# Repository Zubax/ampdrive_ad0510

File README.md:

# AmpDrive AD0510 / Zubax Komar

Zubax Komar is a high-quality FOC ESC based on [Telega](https://zubax.com/technologies/telega) motor control technology.
Komar is designed to support the propulsion systems of light unmanned aerial vehicles (UAVs), unmanned underwater vehicles (UUVs)
and unmanned surface vehicles (USVs). Komar is compatible with almost all PMSM and BLDC motors.
It is designed to be a part of an integrated drive but allows operation as a separate unit as well.
Komar is one of the reference designs for the [Mitochondrik LV](https://zubax.com/products/mitochondrik-lv) control module.

## Brief specs

* 12...51 V input voltage range (4...12S LiCoO<sub>2</sub> battery).
* Up to 2500 W output power (with 12S LiCoO<sub>2</sub> battery).
* Maximum continuous phase current amplitude 100 A.
* A software-controllable 5 V BEC.
* Built-in motor temperature sensor for enhanced self-diagnostics.
* Komar supports a rich set of communication interfaces:
  * Double redundant CAN bus interface.
  * USB Micro-B interface for control, management, and telemetry.
  * Industry-standard RC PWM input.
* Komar is built using highly reliable automotive-grade AEC-Q qualified components.
* Operating device temperature - -40..85 °C.
* Operating humidity - 0..100 %RH (Condensation not permitted).
* Weight - 96.5 g (cables not included).

Due to its superb efficiency, Komar can operate at high power levels using only a very lightweight and compact heatsink to cool the device down.

Komar is designed to be a part of an integrated drive for mid-power motors.
It is best suited for motors with the following specs:

* Continuous power: 2.5 kW
* Continuous phase current amplitude: 90 A
* Outer diameter: 80 mm

Komar can also be used as a separate unit. In this case, a custom phase connector mounted on the housing may be used to provide motor connections.

The parameters of the Aux port are as follows:

* $V_\text{pull}=3.3V$ (defined by Mitochondrik)
* $R_\text{pull}=1200\Omega$ (defined by Mitochondrik)
* $R_\text{io}=200\Omega$ at the Aux connector
* $R_\text{io}=0\Omega$ at the through-hole motor thermistor pin on the PCB (see schematics)

## Construction and usage

Komar itself consists of a power stage PCB with Mitochondrik and the housing (aluminum enclosure plus several plastic parts).
The PCB may use several optional 3D-printed parts that don't influence its properties directly, but may improve the overall user experience:

- Lightpipe
- Capacitor support

## Connections and indication

All connections (except the phase connector) and indicators are presented on the bottom cover, as shown in figure below.

Pinout of connectors is presented in the tables below. 

### CAN1 & CAN2 connectors (type JST BM04B-GHS)

| Pin # | Type  | Name  | Comments                                        |
|-------|-------|-------|-------------------------------------------------|
| 1     | Power | PWR   | BEC 5V power output. Activated in the firmware. |
| 2     | I/O   | CAN_H |                                                 |
| 3     | I/O   | CAN_L |                                                 |
| 4     | Power | GND   |                                                 |

The device does not terminate the CAN bus internally.
If the bus is not redundant, only CAN1 (the primary CAN bus interface) can be used.

### AUX connector (type JST BM04B-GHS)

| Pin # | Type  | Name  | Comments                          |
|-------|-------|-------|-----------------------------------|
| 1     | Power | PWR   | 5V line output                    |
| 2     | I/O   | GPIO1 | GPIO/RCPWM input/Thermistor input |
| 3     | I/O   | GPIO2 |                                   |
| 4     | Power | GND   |                                   |

The motor windings temperature can be measured by means of a PTC thermistor. The following thermistors can be connected between GPIO1 and GND:

- KTY84/130
- KTY81/120
- KTY83/120

No additional components are needed for the thermistor. The thermistor model is selected in the firmware.

### USB connector

Common USB 2.0 Micro-USB connector is dedicated for the device configuration and control using the [Kucher GUI](https://files.zubax.com/products/com.zubax.kucher/1.0.0/).

## Thermal performance

Thermal simulation is performed under the following conditions:

* The heat source is applied to the heatsink area where the PCB is placed. Its power is 78.5 W.
  It is a typical value of power losses in the Komar power stage when operating at a power level of 2500 W
  and powered from a discharged 12S battery (~40 V). This should represent the worst-case scenario.

* Ambient temperature is 20 °C.

* The convection value of 350 W/(m<sup>2</sup>K) is established empirically after conducting several experiments with real hardware.

## Mounting pattern

## VSI Configuration

All Komars with Telega v1 (Cyphal) are configured with the following VSI parameters by default.

```
sys.golden:               sys. vsi.
vsi.bridge_resistance:    [0.002, 0.003, 0.002, 0.003, 0.002, 0.002]
vsi.phase_current_gain:   [100, 100,  25,  25]
vsi.phase_current_stderr: [0.3, 0.3, 0.2, 0.2]
vsi.thermistor_v2k:       [223.15, 100.0, 0.0]
```

Please refer to the manufacturing manual and schematics for further information.
The most up-to-date documentation is attached to the latest published
[release package](https://github.com/Zubax/Komar/releases).

## Release notes

Newest entries at the top.

### Komar v1.6 (work in progress)

* The USB connector will no longer be installed, as USB is not supported in Telega v1.
* to be continued...

### Komar v1.5 (January 2023)

* Updated alternative for MCP9700AT-E/TTVAO to MCP9700T-E/TT.

### Komar v1.4 (January 2023)

* Removed alternative for Diode BAV99HDWQ-13.
* Increased the hardware over-current protection trip level to 427A.

### Komar v1.3 (November 2022)

* Changed DC/Battery power wire to 12 AWG in the assembly manual.
* Corrected Micro USB attributes in the schematic.
* Added alternative parts:

| Part               | Alternative       | Function          |
| -------------------| ------------------| ------------------|
| ATA6561-GBQW-N     | TJA1441DTK/0Z     | CAN TRANSCEIVER   |
| FDMS86368-F085     | BSC080N12LSGATMA1 | FET               |
| BAV99HDWQ-13       | BAV70HDWQ-13      | DIODE             |
| MCP9700AT-E/TTVAO  | MCP9701T-E/TT     | THERMISTOR        |
| ELXZ630ELL331MK20S | EEU-FC1J331B      | CAPACITOR         |
| NRVB120VLSFT1G     | NRVB230LSFT1G     | DIODE             |

### Komar v1.2 (July 2021)

* USB connector with mounting pads swaped with through-hole USB connector to ensure durability.
* Manufacturing instructions update.
* New design of the phase connector.
* Phase connector manufacturing instructions and jig added.
* A better design of the PCB spacer added.

### Komar v1.1 (August 2020)

* Panel template fix: solder mask issue with phase connectors pads fixed (#13).
* Enclosure: increase chamfering depth (#14).

### Komar v1.0 (July 2020)

#### Major PCB updates

* All components are AEC-Q qualified to be compatible with the hardware design policies.
* Better and bigger bulk capacitors.
* Holes for adding 3D-printed capacitor supports added; capacitor supports  developed (not shown on the PCB).
* All the gate networks re-routed and greatly improved.
* All the LEDs grouped in one place; holes for mounting lightpipe added.
* Holes diameter for power supply wires soldering greatly increased to fit any 3.3 sqmm multi-stand wire.
* Holes diameter for phase wires increased to fit either any 2 sqmm multi-stand wire
  (in the case of motor soldering to the PCB) or 3.3 sqmm single-strand wire (if phase connectors are used).
* Overcurrent protection trip level increased 1.5 times to theoretical value of 200 A.
  In practice, however, the overcurrent protection tends to trip at approx. 20-30% below the configured level
  due to the temperature drift of the MOSFETs R<sub>DS(on)</sub> and RF noise.
* TVS diodes with a lower reverse standoff voltage are used (51 V).

#### Major housing changes

* The housing parts are now held together with 4 M3.5 screws instead of M3.
* The housing itself is now mounted on the chassis using 4x M4 screws (was M3).
* Wall thickness of the top part of the housing increased from 1 to 1.6 mm.
* The connector window is slightly smaller now.
* A totally different construction of the phase connector.
  It is much bigger and accepts bullet connectors up to 6 mm (previously, 3.5 mm bullet connectors were used).
* Phase connector is now supposed to use single-stranded thick stiff copper wires instead of flexible multi-stranded ones.
* All the LEDs are grouped in one place now. The holes for the LEDs have been moved.
* Lightpipe for the LEDs added (will be manufactured inhouse using 3d printing).
* 3D-printed spacers between the PCB and the housing added.
* Slightly improved the heatsink efficiency by redesigning the fins.
* 3x M2.5 holes for mounting optional (and not yet developed) connector protection cap added.
* Optional power connector assembly  mount added.

### Komar v0.2 (2018)

First release that was actually manufactured.

### License

This project is licensed under the terms of [CC-BY 4.0](https://creativecommons.org/licenses/by/4.0/).

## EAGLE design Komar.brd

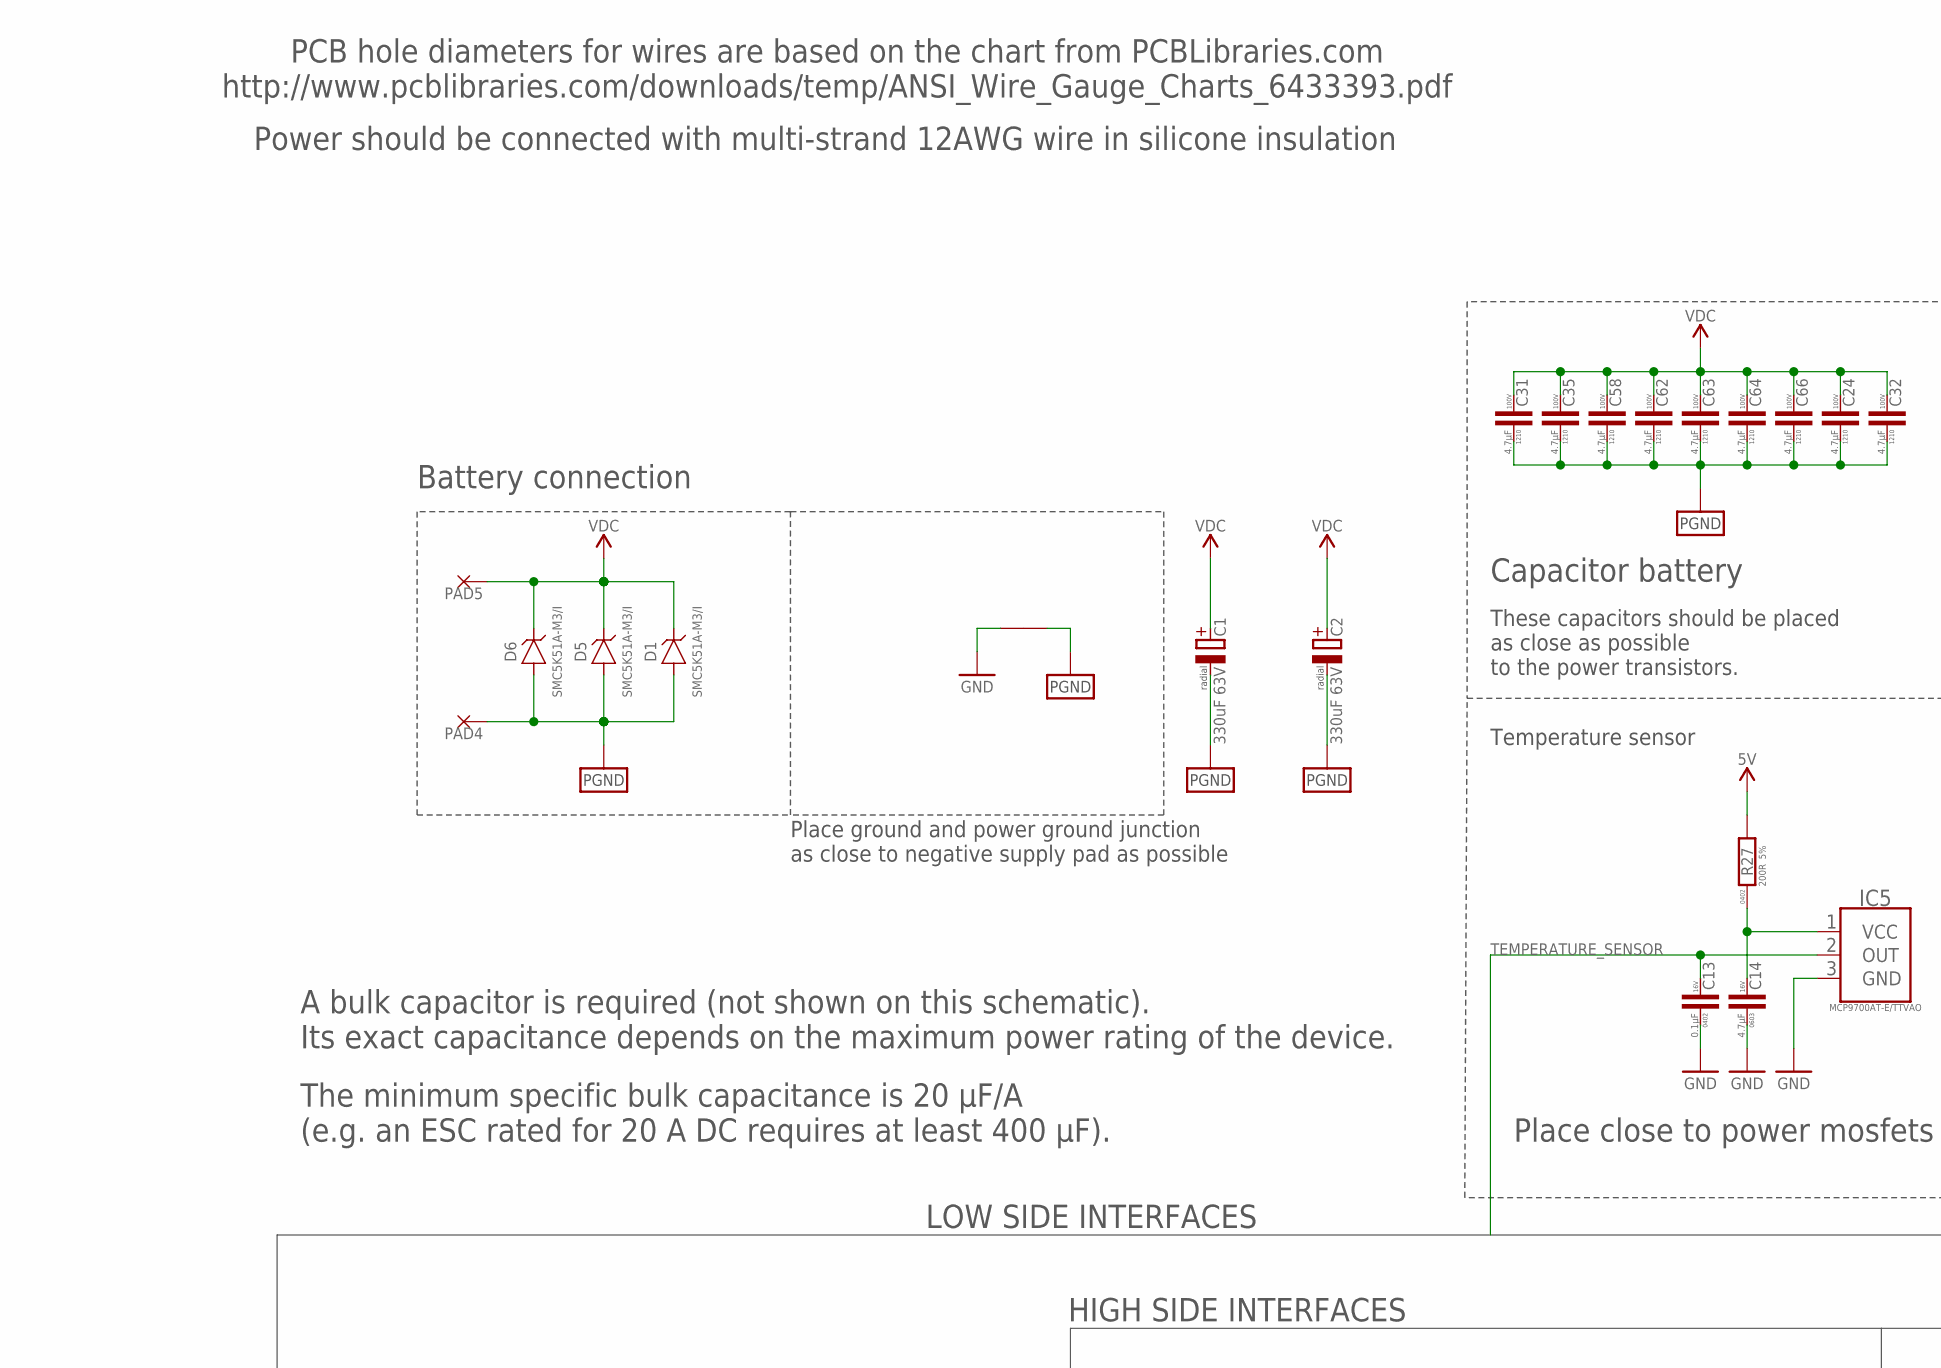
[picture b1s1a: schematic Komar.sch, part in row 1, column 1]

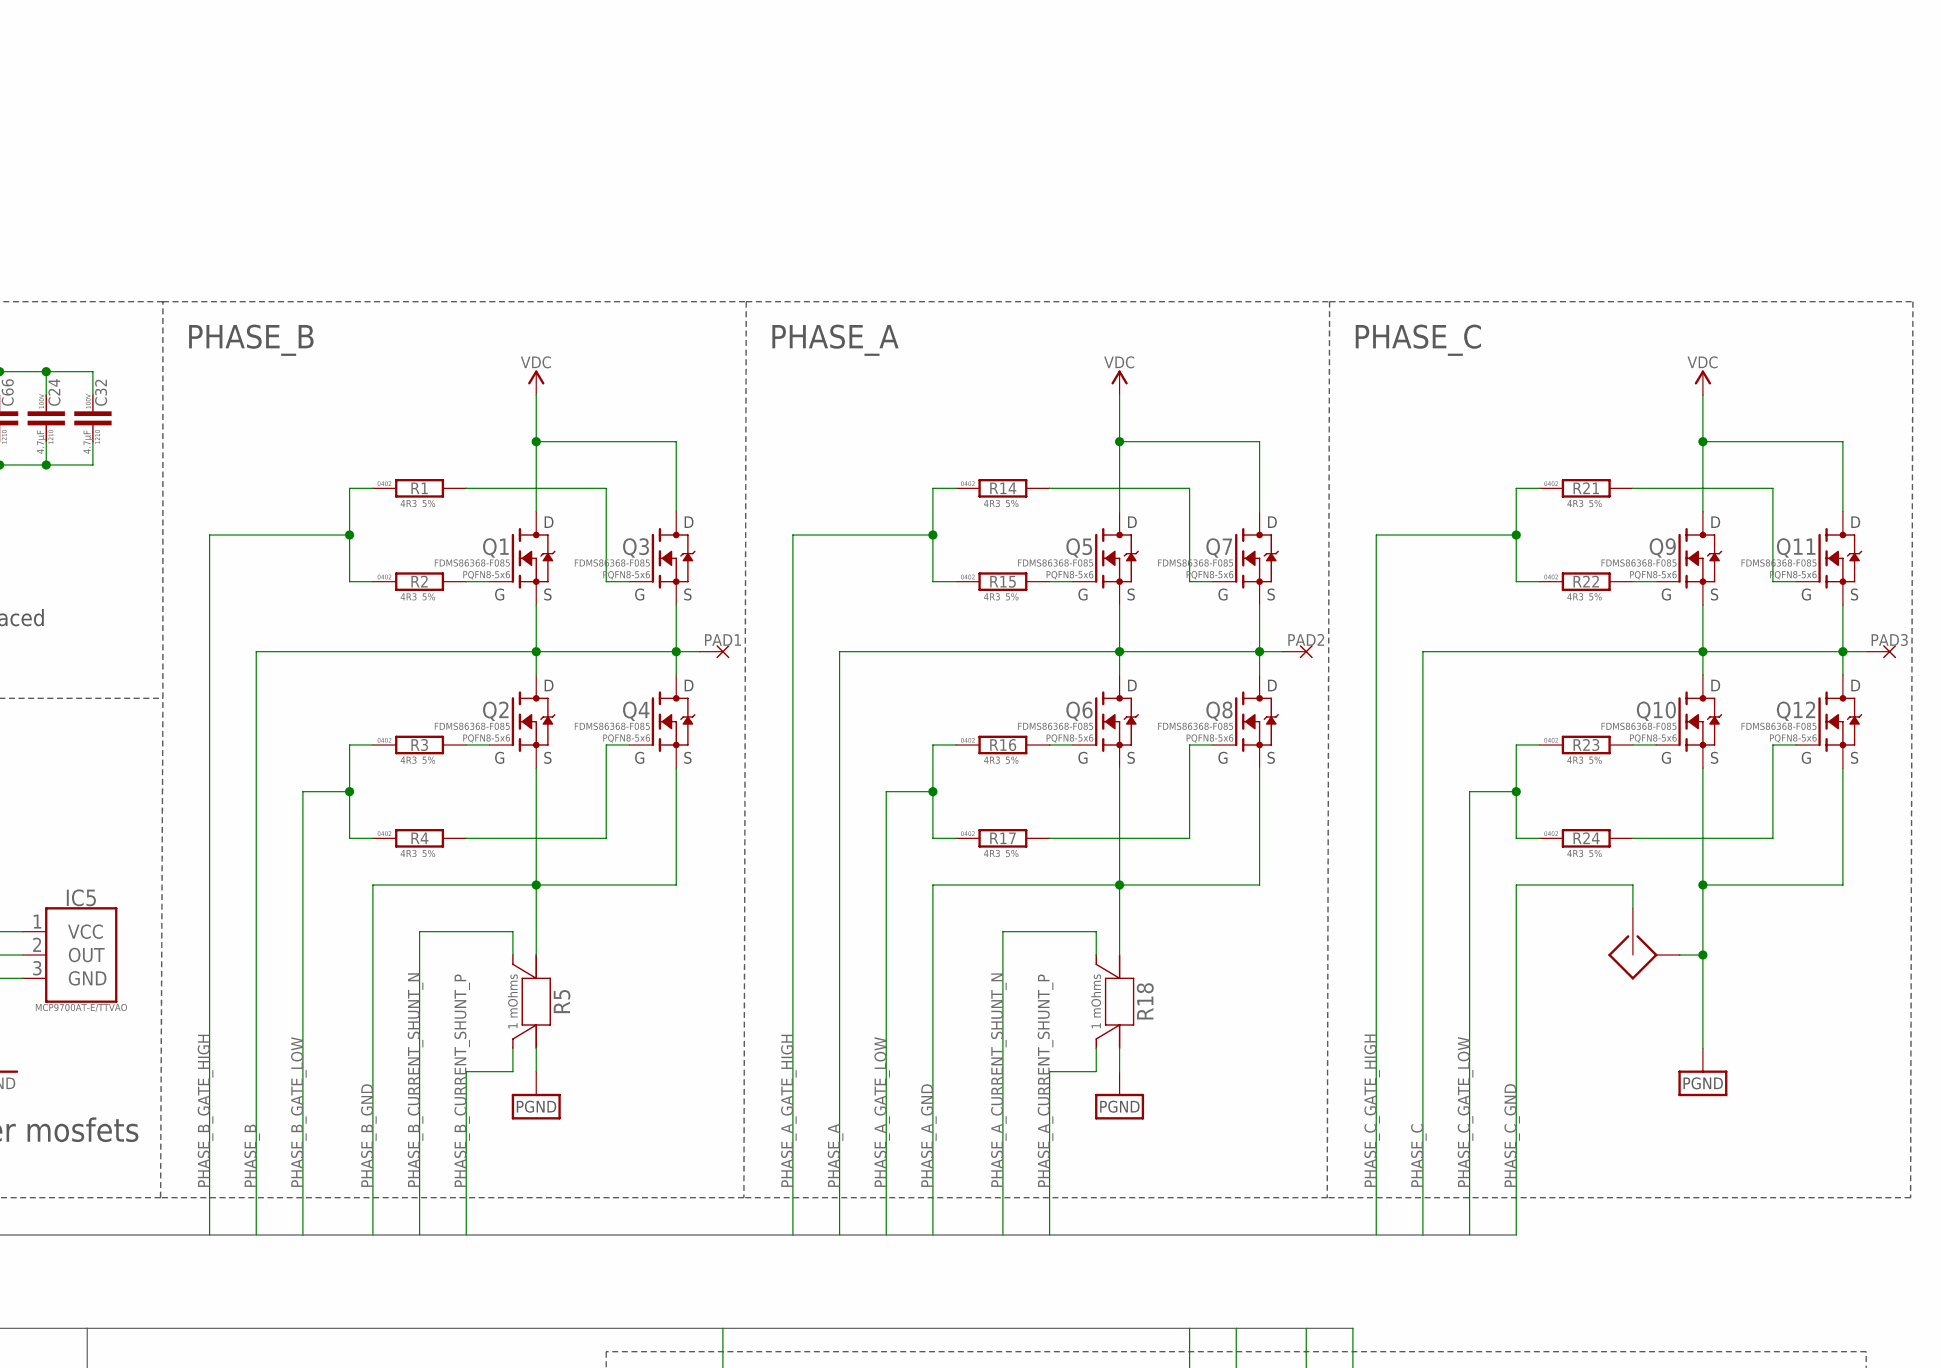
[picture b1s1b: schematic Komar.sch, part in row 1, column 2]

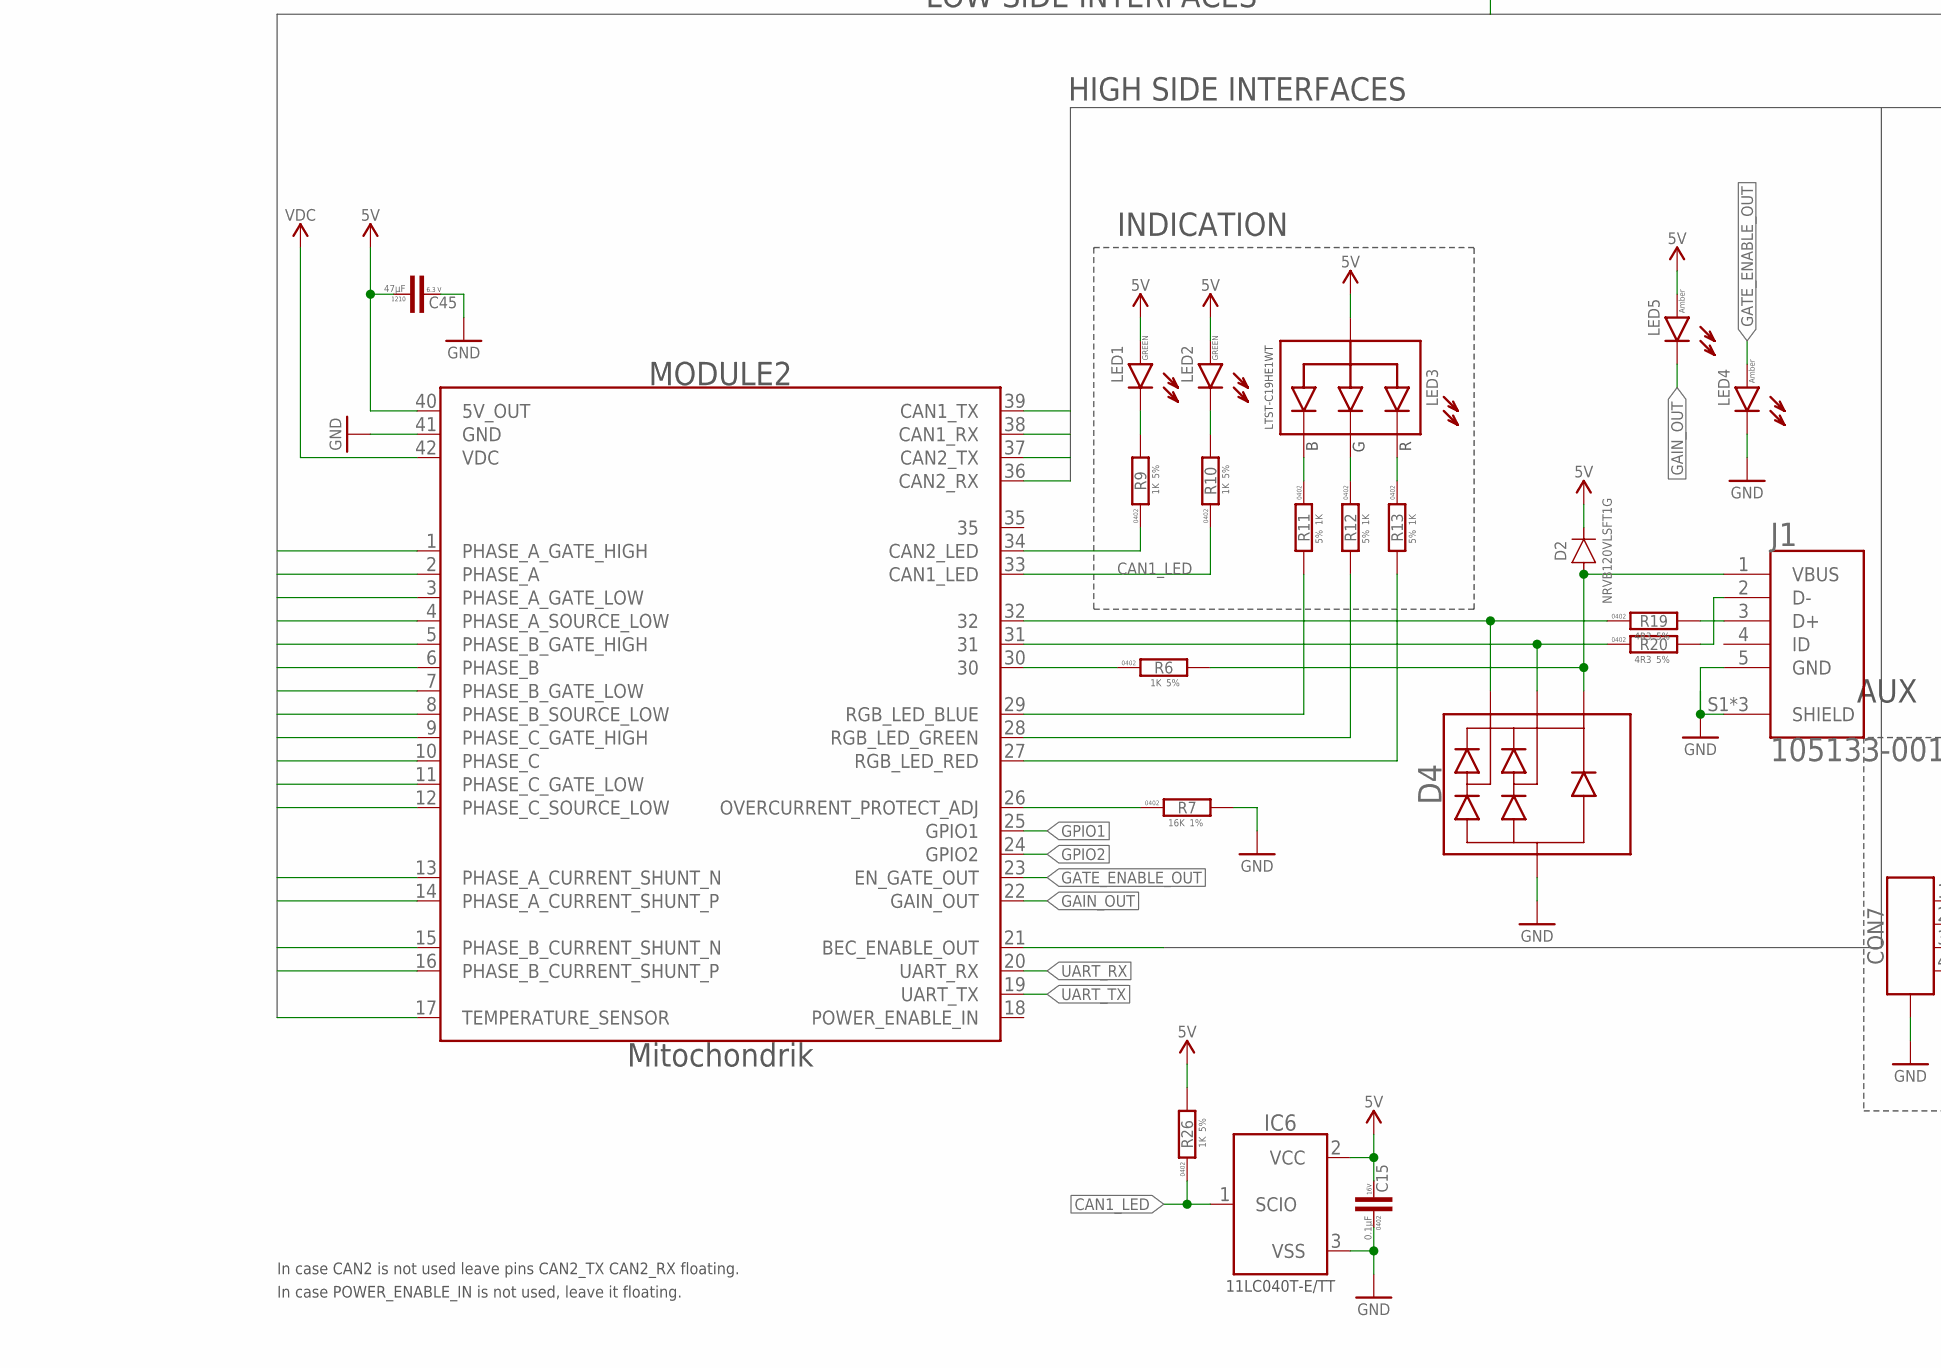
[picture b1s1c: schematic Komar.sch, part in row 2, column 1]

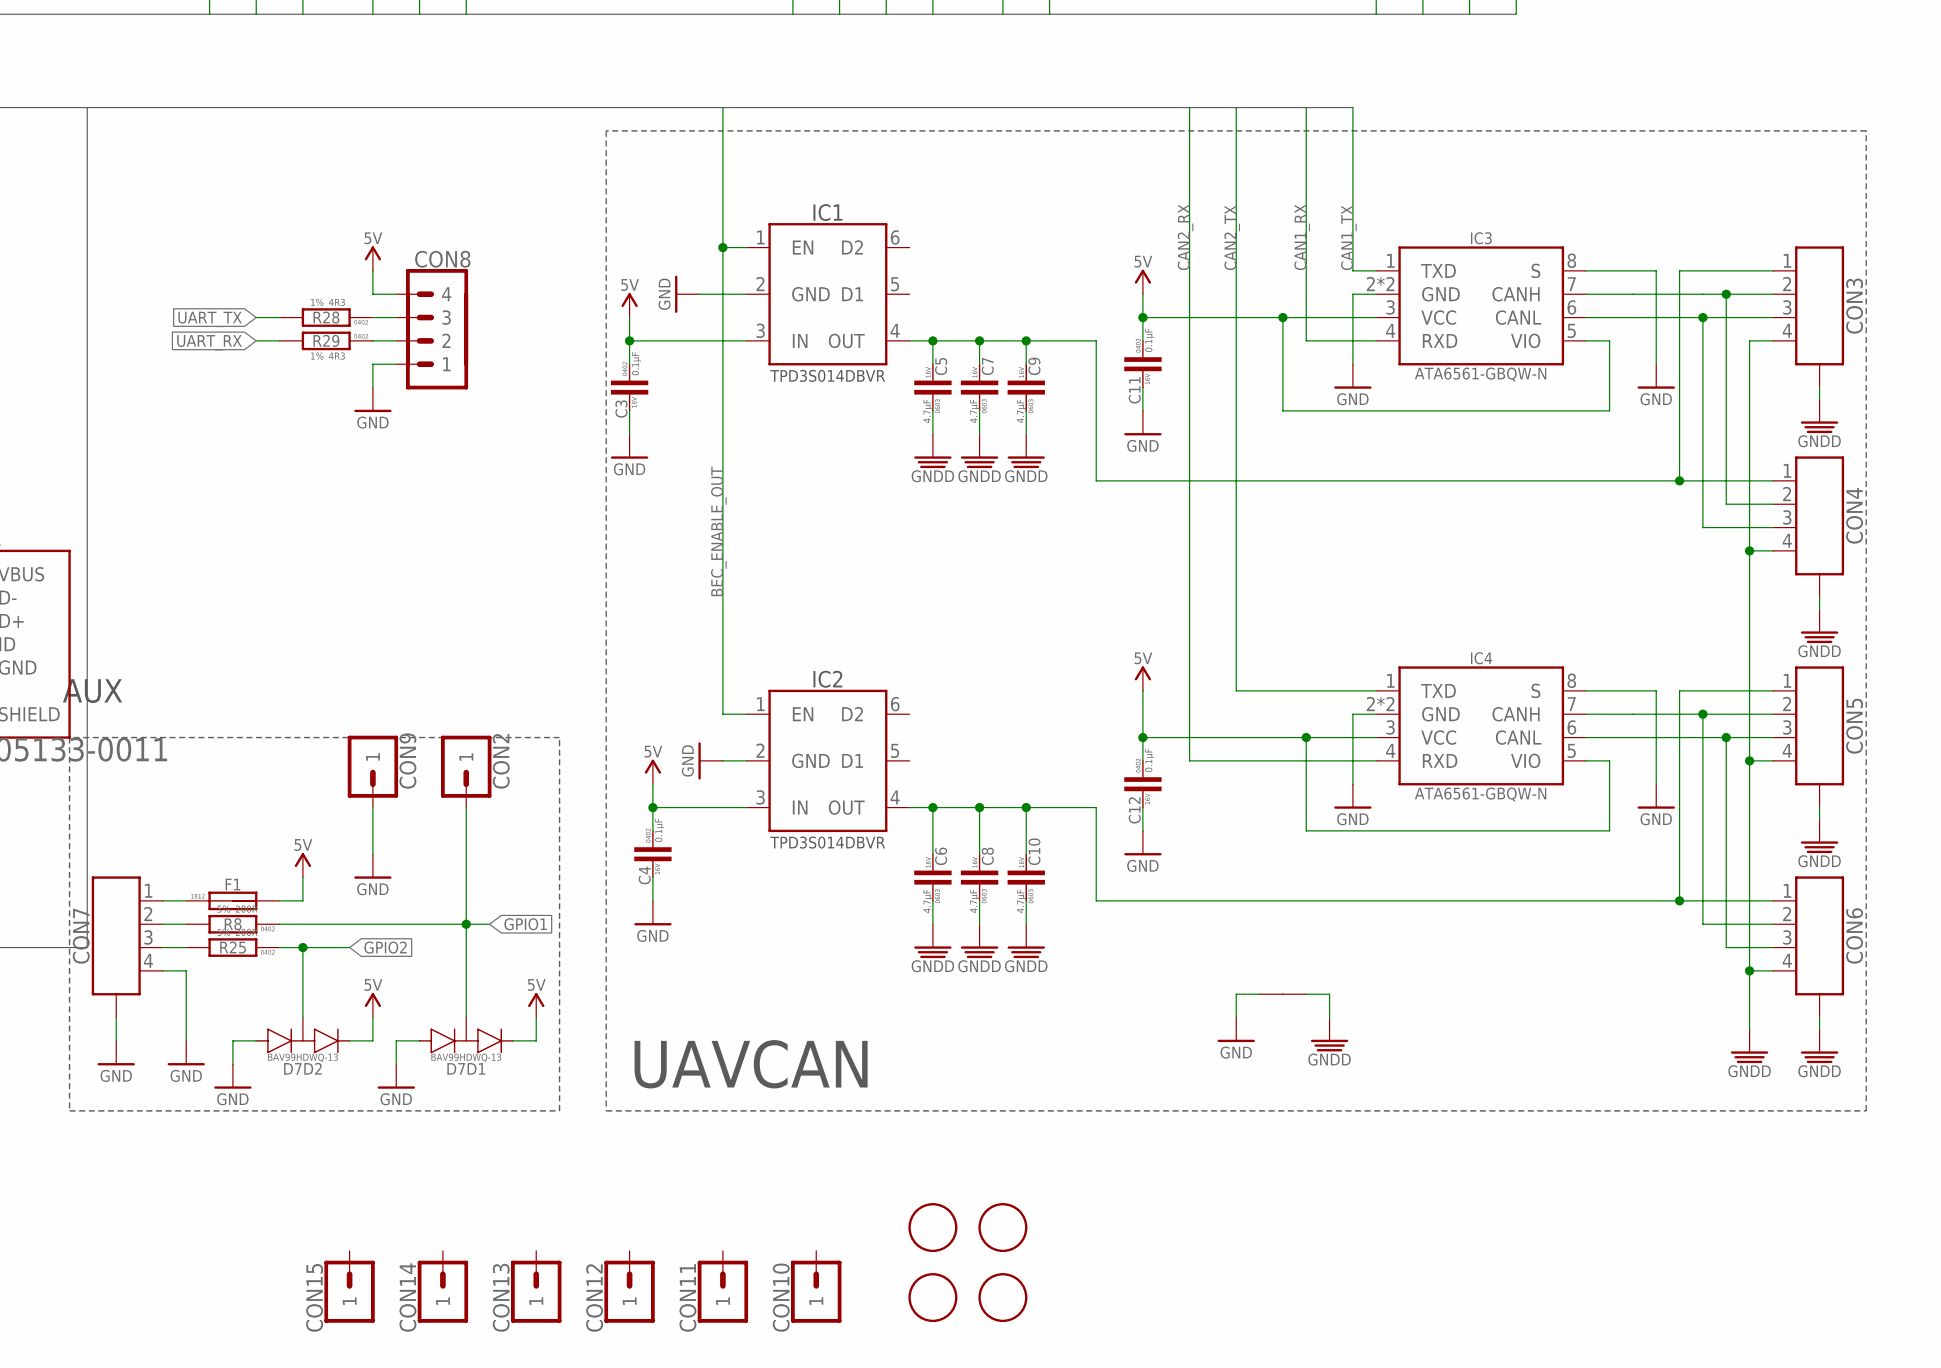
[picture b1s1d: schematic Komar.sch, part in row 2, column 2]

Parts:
C1, C2: 330uF 63V; SIDE_10X22; DIGIKEY# 565-2043-ND
C3, C4, C11, C12, C13, C15: 0.1µF; C0402; VOLTAGE 16V; DIGIKEY# 490-7998-1-ND
C5, C6, C7, C8, C9, C10, C14: 4.7µF; C0603; VOLTAGE 16V; DIGIKEY# 490-12289-1-ND
C24, C31, C32, C35, C58, C62, C63, C64, C66: 4.7µF; C1210; VOLTAGE 100V; DIGIKEY# 490-14484-1-ND
C45: 47µF; C1210; VOLTAGE 6.3 V; DIGIKEY# 490-4844-1-ND
CON2, CON9, CON10, CON11, CON12, CON13, CON14, CON15: PINHEAD_1X01-2; 1X01-PTH-2
CON3, CON4, CON5, CON6, CON7: CON-4P-TABS-STRAIGHT; JST_GH-4P-STRAIGHT
CON8: PINHEAD_1X04-2; 1X04-PTH-2
D1, D5, D6: SMC5K51A-M3/I; DO-214AB(SMC)
D2: NRVB120VLSFT1G; SOD123F
D4: DRTR5V0U2SR-7; SOT143B
D7: BAV99HDWQ-13; SOT363
F1: FUSE-1812; F1812; DIGIKEY# MF-MSMF010-2CT-ND
IC1, IC2: TPD3S014DBVR-SOT23-6; SOT26
IC3, IC4: ATA6561-GBQW-N-HVSON8; SOT782-1
IC5: MCP9700AT-E/TTVAO-SOT23; SOT23B-3
IC6: 11LC040T-E/TT; SOT23B-3
J1: 105133-0011; MOLEX_105133-0011; DIGIKEY# WM10134TR-ND
LED1, LED2: GREEN; LED0402; DIGIKEY# 1830-IN-S42BT5GCT-ND
LED3: LTST-C19HE1WT; 0606
LED4, LED5: ORANGE; LED0402; DIGIKEY# 1830-IN-S42BT5ACT-ND
MODULE2: MITOHONDRIQUE_V0.3-TH; MITOHONDRIQUE-TH
PAD1, PAD2, PAD3: PAD-HOLE_2.4_SQUARE; HOLE_2.4
PAD4, PAD5: PAD-HOLE_2.8_SQUARE; HOLE_2.8
Q1, Q2, Q3, Q4, Q5, Q6, Q7, Q8, Q9, Q10, Q11, Q12: FDMS86368-F085; PQFN8_5X6
R1, R2, R3, R4, R14, R15, R16, R17, R19, R20, R21, R22, R23, R24: 4R3; R0402; DIGIKEY# P4.3JCT-ND
R5, R18: 1 mOhms; R2512-KELVIN; DIGIKEY# CRE2512-FZ-R001E-3CT-ND
R6, R9, R10, R11, R12, R13, R26: 1K; R0402; DIGIKEY# P1.00KLCT-ND
R7: 16K; R0402; DIGIKEY# P124444CT-ND
R8, R25, R27: 200R; R0402; DIGIKEY# P200JCT-ND
R28, R29: 4R3; R0402; DIGIKEY# 2
S1: SENSE; SENSE-0.6
U$1, U$3: CONNECTION-SMD; CONNECTION
U$5, U$6, U$7, U$11: FIDUCIALMOUNT; FIDUCIA-MOUNT

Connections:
AGH1: Q7.4 (G), R14.2
AGH2: Q5.4 (G), R15.2
AGL1: Q8.4 (G), R17.2
AGL2: Q6.4 (G), R16.2
BEC_ENABLE_OUT: IC1.1 (EN), IC2.1 (EN), MODULE2.21 (BEC_ENABLE_OUT)
BGH1: Q3.4 (G), R1.2
BGH2: Q1.4 (G), R2.2
BGL1: Q4.4 (G), R4.2
BGL2: Q2.4 (G), R3.2
CAN1_LED: IC6.1 (SCIO), MODULE2.33 (CAN1_LED), R10.1, R26.1
CAN1_RX: IC3.4 (RXD), MODULE2.38 (CAN1_RX)
CAN1_TX: IC3.1 (TXD), MODULE2.39 (CAN1_TX)
CAN1_VDD: C5.2, C7.2, C9.2, CON3.1, CON4.1, IC1.4 (OUT)
CAN2_LED: MODULE2.34 (CAN2_LED), R9.1
CAN2_RX: IC4.4 (RXD), MODULE2.36 (CAN2_RX)
CAN2_TX: IC4.1 (TXD), MODULE2.37 (CAN2_TX)
CAN2_VDD: C6.2, C8.2, C10.2, CON5.1, CON6.1, IC2.4 (OUT)
CGH1: Q11.4 (G), R21.2
CGH2: Q9.4 (G), R22.2
CGL1: Q12.4 (G), R24.2
CGL2: Q10.4 (G), R23.2
GAIN_OUT: LED5.C, MODULE2.22 (GAIN_OUT)
GATE_ENABLE_OUT: LED4.A, MODULE2.23 (EN_GATE_OUT)
GND: C3.2, C4.2, C11.2, C12.2, C13.1, C14.1, C15.1, C45.2, CON7.4, CON7.M$0 (GND), CON7.M$1 (GND), CON8.1, CON9.1, D4.1 (C), D7.1 (A), D7.4 (A), IC1.2 (GND), IC2.2 (GND), IC3.2 (GND), IC3.8 (S), IC3.PAD (GND), IC4.2 (GND), IC4.8 (S), IC4.PAD (GND), IC5.3 (GND), IC6.3 (VSS), J1.5 (GND), J1.S1 (SHIELD), J1.S2 (SHIELD), J1.S3 (SHIELD), LED4.C, MODULE2.41 (GND), R7.2, U$1.P$1, U$3.P$1
GNDD: C5.1, C6.1, C7.1, C8.1, C9.1, C10.1, CON3.4, CON3.M$0 (GND), CON3.M$1 (GND), CON4.4, CON4.M$0 (GND), CON4.M$1 (GND), CON5.4, CON5.M$0 (GND), CON5.M$1 (GND), CON6.4, CON6.M$0 (GND), CON6.M$1 (GND), U$1.P$2
GPIO1: CON2.1, D7.6 (COMMON), MODULE2.25 (GPIO1), R8.1
GPIO2: D7.3 (COMMON), MODULE2.24 (GPIO2), R25.1
LED_BLUE: MODULE2.29 (RGB_LED_BLUE), R11.2
LED_GREEN: MODULE2.28 (RGB_LED_GREEN), R12.2
LED_RED: MODULE2.27 (RGB_LED_RED), R13.2
unnamed: J1.3 (D+), R19.2
unnamed: J1.2 (D-), R20.2
unnamed: MODULE2.30, R6.1
unnamed: CON7.1, F1.P$1 (1)
unnamed: C14.2, IC5.1 (VCC), R27.1
unnamed: LED2.C, R10.2
unnamed: LED1.C, R9.2
unnamed: MODULE2.26 (OVERCURRENT_PROTECT_ADJ), R7.1
unnamed: CON7.2, R8.2
unnamed: CON7.3, R25.2
unnamed: CON3.2, CON4.2, IC3.7 (CANH)
unnamed: CON3.3, CON4.3, IC3.6 (CANL)
unnamed: CON8.3, R28.1
unnamed: CON8.2, R29.1
unnamed: CON5.3, CON6.3, IC4.6 (CANL)
unnamed: CON5.2, CON6.2, IC4.7 (CANH)
unnamed: D4.3 (D2), MODULE2.31, R20.1
unnamed: D4.2 (D1), MODULE2.32, R19.1
unnamed: LED3.R, R13.1
unnamed: LED3.G, R12.1
unnamed: LED3.B, R11.1
PGND: C1.-, C2.-, C24.1, C31.1, C32.1, C35.1, C58.1, C62.1, C63.1, C64.1, C66.1, D1.A, D5.A, D6.A, PAD4.1, Q10.1 (S), Q10.2 (S), Q10.3 (S), Q12.1 (S), Q12.2 (S), Q12.3 (S), R5.2, R5.22 (2), R18.2, R18.22 (2), S1.SHELL (SHELLL), U$3.P$2
PHASE_A: MODULE2.2 (PHASE_A), PAD2.1, Q5.1 (S), Q5.2 (S), Q5.3 (S), Q6.5 (D), Q6.6 (D), Q6.7 (D), Q6.8 (D), Q6.P$1 (D), Q7.1 (S), Q7.2 (S), Q7.3 (S), Q8.5 (D), Q8.6 (D), Q8.7 (D), Q8.8 (D), Q8.P$1 (D)
PHASE_A_CURRENT_SHUNT_N: MODULE2.13 (PHASE_A_CURRENT_SHUNT_N), R18.S1
PHASE_A_CURRENT_SHUNT_P: MODULE2.14 (PHASE_A_CURRENT_SHUNT_P), R18.S2
PHASE_A_GATE_HIGH: MODULE2.1 (PHASE_A_GATE_HIGH), R14.1, R15.1
PHASE_A_GATE_LOW: MODULE2.3 (PHASE_A_GATE_LOW), R16.1, R17.1
PHASE_A_GND: MODULE2.4 (PHASE_A_SOURCE_LOW), Q6.1 (S), Q6.2 (S), Q6.3 (S), Q8.1 (S), Q8.2 (S), Q8.3 (S), R18.1, R18.11 (1)
PHASE_B: MODULE2.6 (PHASE_B), PAD1.1, Q1.1 (S), Q1.2 (S), Q1.3 (S), Q2.5 (D), Q2.6 (D), Q2.7 (D), Q2.8 (D), Q2.P$1 (D), Q3.1 (S), Q3.2 (S), Q3.3 (S), Q4.5 (D), Q4.6 (D), Q4.7 (D), Q4.8 (D), Q4.P$1 (D)
PHASE_B_CURRENT_SHUNT_N: MODULE2.15 (PHASE_B_CURRENT_SHUNT_N), R5.S1
PHASE_B_CURRENT_SHUNT_P: MODULE2.16 (PHASE_B_CURRENT_SHUNT_P), R5.S2
PHASE_B_GATE_HIGH: MODULE2.5 (PHASE_B_GATE_HIGH), R1.1, R2.1
PHASE_B_GATE_LOW: MODULE2.7 (PHASE_B_GATE_LOW), R3.1, R4.1
PHASE_B_GND: MODULE2.8 (PHASE_B_SOURCE_LOW), Q2.1 (S), Q2.2 (S), Q2.3 (S), Q4.1 (S), Q4.2 (S), Q4.3 (S), R5.1, R5.11 (1)
PHASE_C: MODULE2.10 (PHASE_C), PAD3.1, Q9.1 (S), Q9.2 (S), Q9.3 (S), Q10.5 (D), Q10.6 (D), Q10.7 (D), Q10.8 (D), Q10.P$1 (D), Q11.1 (S), Q11.2 (S), Q11.3 (S), Q12.5 (D), Q12.6 (D), Q12.7 (D), Q12.8 (D), Q12.P$1 (D)
PHASE_C_GATE_HIGH: MODULE2.9 (PHASE_C_GATE_HIGH), R21.1, R22.1
PHASE_C_GATE_LOW: MODULE2.11 (PHASE_C_GATE_LOW), R23.1, R24.1
PHASE_C_GND: MODULE2.12 (PHASE_C_SOURCE_LOW), S1.IN
TEMPERATURE_SENSOR: C13.2, IC5.2 (OUT), MODULE2.17 (TEMPERATURE_SENSOR)
UART_RX: MODULE2.20 (UART_RX), R29.2
UART_TX: MODULE2.19 (UART_TX), R28.2
USB_VBUS: D2.A, D4.4 (A), J1.1 (VBUS), R6.2
VDC: C1.+, C2.+, C24.2, C31.2, C32.2, C35.2, C58.2, C62.2, C63.2, C64.2, C66.2, D1.C, D5.C, D6.C, MODULE2.42 (VDC), PAD5.1, Q1.5 (D), Q1.6 (D), Q1.7 (D), Q1.8 (D), Q1.P$1 (D), Q3.5 (D), Q3.6 (D), Q3.7 (D), Q3.8 (D), Q3.P$1 (D), Q5.5 (D), Q5.6 (D), Q5.7 (D), Q5.8 (D), Q5.P$1 (D), Q7.5 (D), Q7.6 (D), Q7.7 (D), Q7.8 (D), Q7.P$1 (D), Q9.5 (D), Q9.6 (D), Q9.7 (D), Q9.8 (D), Q9.P$1 (D), Q11.5 (D), Q11.6 (D), Q11.7 (D), Q11.8 (D), Q11.P$1 (D)
VDD_5V: C3.1, C4.1, C11.1, C12.1, C15.2, C45.1, CON8.4, D2.C, D7.2 (C), D7.5 (C), F1.P$2 (2), IC1.3 (IN), IC2.3 (IN), IC3.3 (VCC), IC3.5 (VIO), IC4.3 (VCC), IC4.5 (VIO), IC6.2 (VCC), LED1.A, LED2.A, LED3.+ (A), LED5.A, MODULE2.40 (5V_OUT), R26.2, R27.2

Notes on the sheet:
PHASE_B
PHASE_A
PHASE_C
UAVCAN
INDICATION
A bulk capacitor is required (not shown on this schematic). Its exact capacitance depends on the maximum power rating of the device.
Capacitor battery
These capacitors should be placed as close as possible to the power transistors.
Temperature sensor
Battery connection
The minimum specific bulk capacitance is 20 μF/A (e.g. an ESC rated for 20 A DC requires at least 400 μF).
Place ground and power ground junction as close to negative supply pad as possible
LOW SIDE INTERFACES
HIGH SIDE INTERFACES
In case CAN2 is not used leave pins CAN2_TX CAN2_RX floating.
In case POWER_ENABLE_IN is not used, leave it floating.
Place close to power mosfets
AUX
Power should be connected with multi-strand 12AWG wire in silicone insulation
PCB hole diameters for wires are based on the chart from PCBLibraries.com http://www.pcblibraries.com/downloads/temp/ANSI_Wire_Gauge_Charts_6433393.pdf

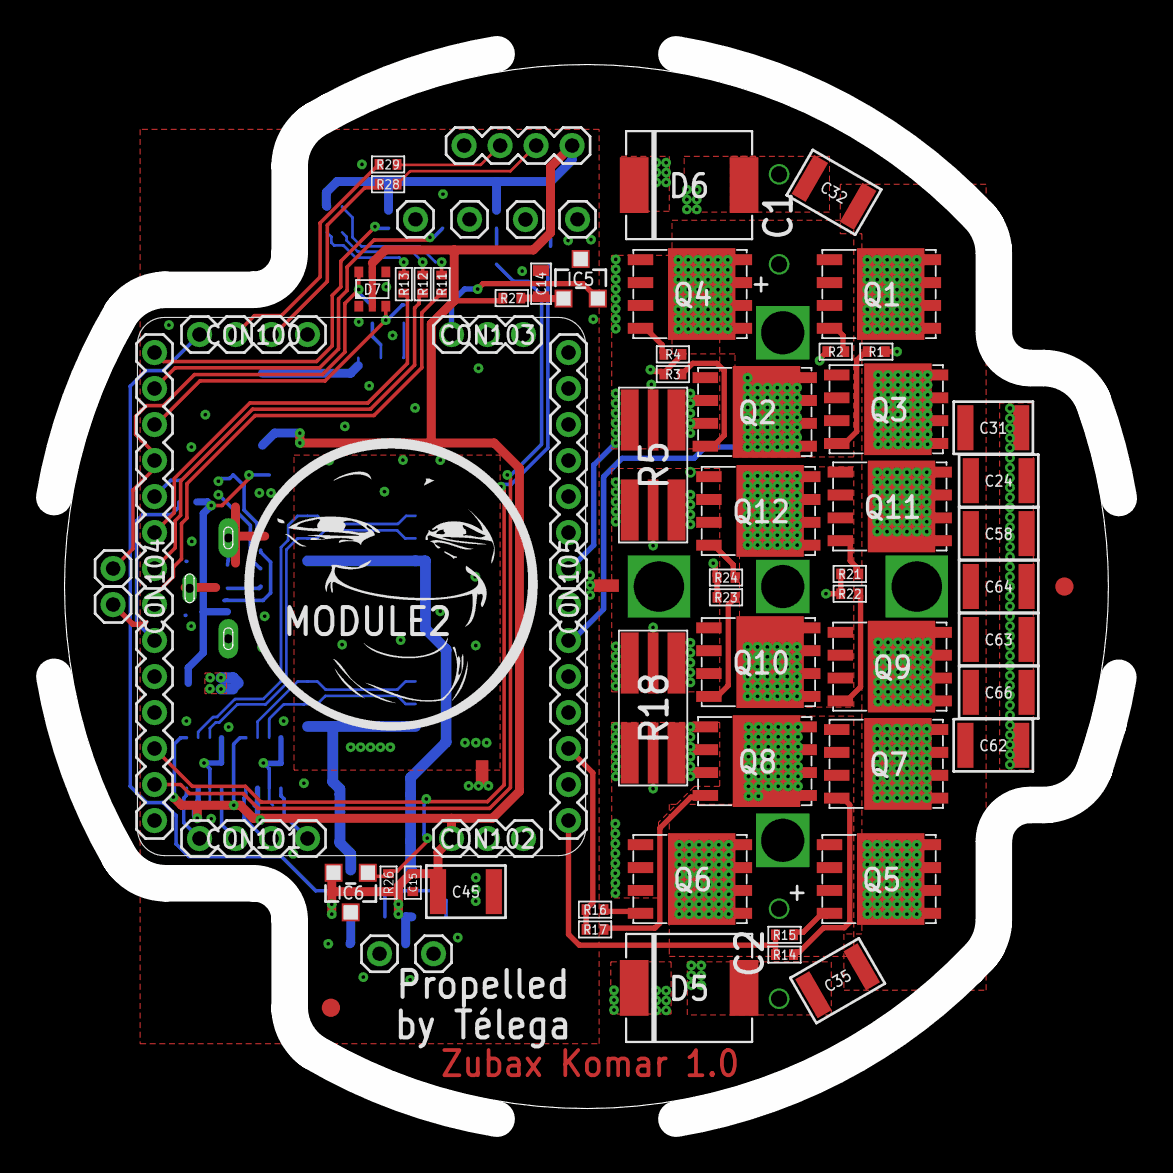
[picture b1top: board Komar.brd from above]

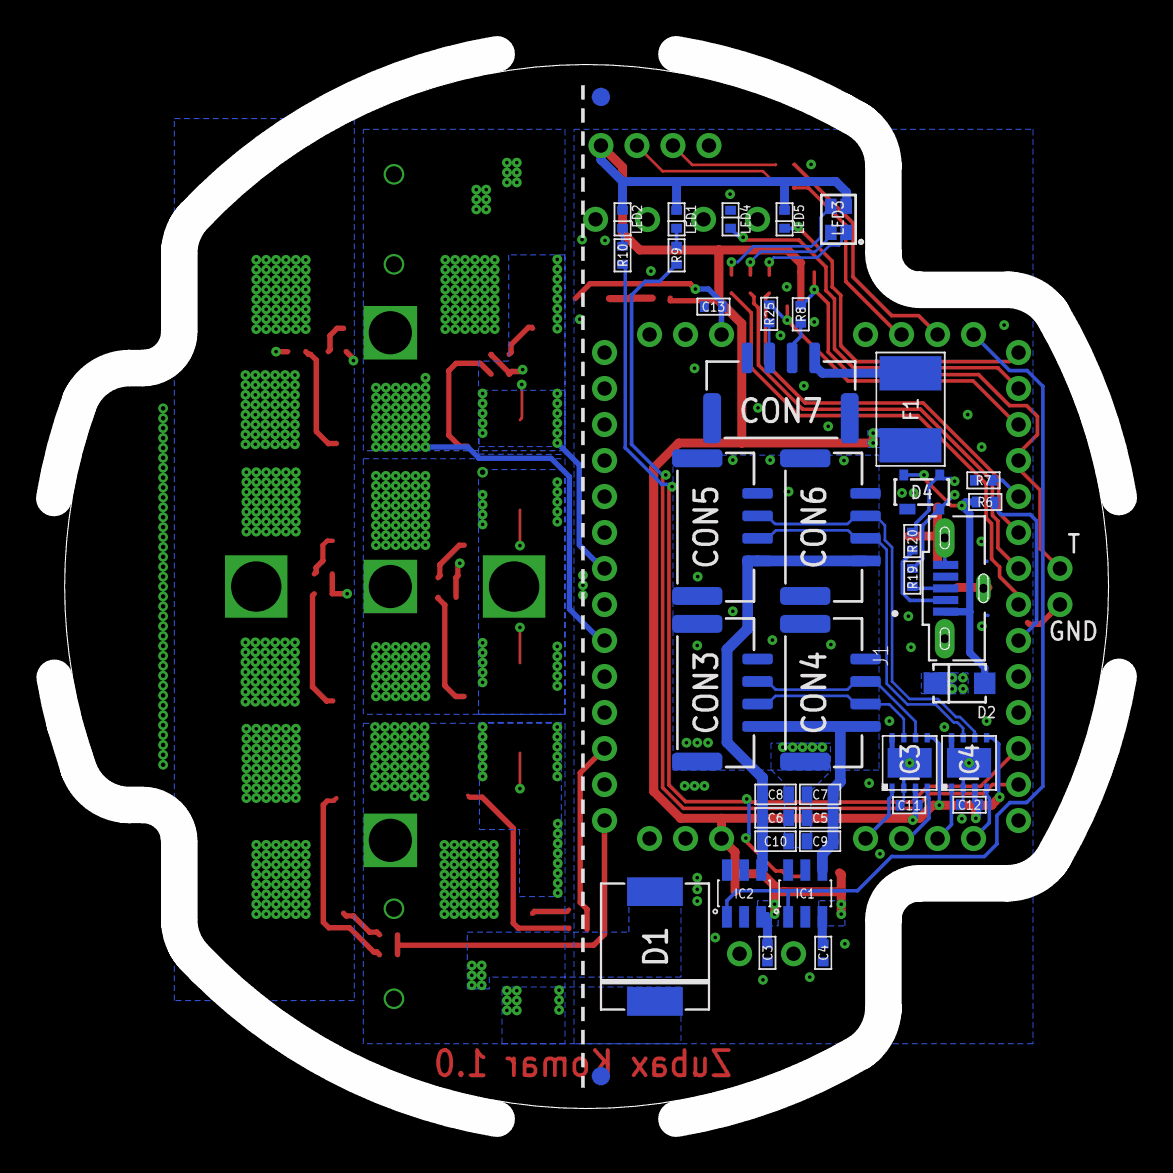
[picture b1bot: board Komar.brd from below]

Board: 4 copper layers, 59.2 x 59.2 mm, 113 parts (40 on the bottom side), 74 nets.

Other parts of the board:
U$2: YOBA_17X17
